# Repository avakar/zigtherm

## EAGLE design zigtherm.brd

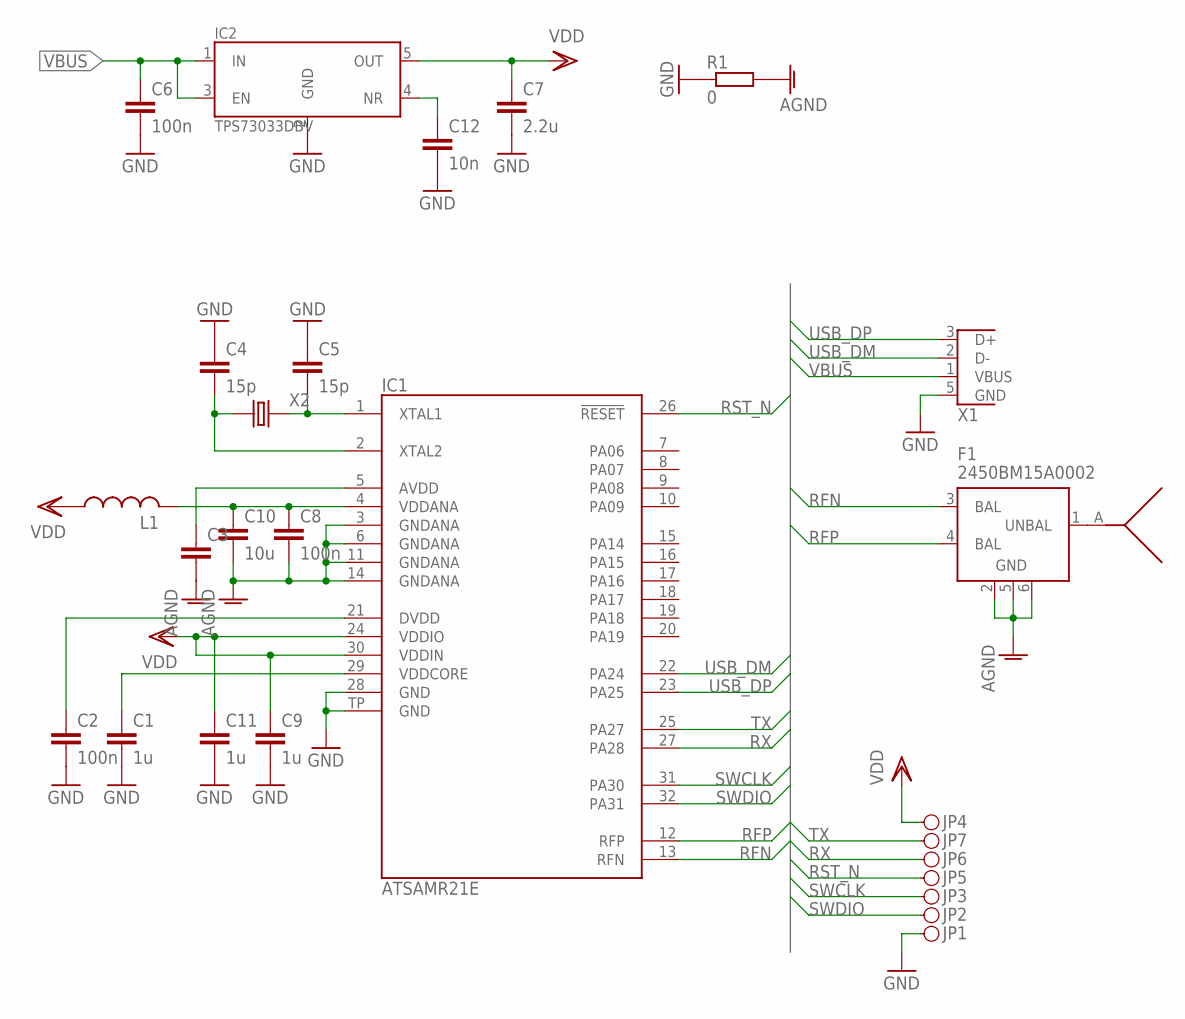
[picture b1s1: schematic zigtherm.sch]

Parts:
AE1: INVERTED_F_ANTENNA
C1, C9, C11: 1u; C0603
C2, C6, C8: 100n; C0603
C3: C-EUC0603; C0603
C4, C5: 15p; C0603
C7: 2.2u; C0603
C10: 10u; C0603
C12: 10n; C0603
F1: 2450BM15A0002
IC1: ATSAMR21E; QFN32
IC2: TPS73033DBV; SOT23-DBV
JP1, JP2, JP3, JP4, JP5, JP6, JP7: PINH1X01SMD
L1: L-USL2012C; L2012C
R1: 0; R0603
X1: USB-MICRO-B-BOTTOM-MOLEX
X2: XTAL3.2X2.5; 3.2X2.5

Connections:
AGND: C3.2, C8.2, C10.2, F1.2 (GND), F1.5 (GND), F1.6 (GND), IC1.3 (GNDANA), IC1.6 (GNDANA), IC1.11 (GNDANA), IC1.14 (GNDANA), R1.2
AVDD: C3.1, IC1.5 (AVDD)
DVDD: C2.1, IC1.21 (DVDD)
GND: C1.2, C2.2, C4.1, C5.1, C6.2, C7.2, C9.2, C11.2, C12.2, IC1.28 (GND), IC1.TP (GND), IC2.2 (GND), JP1.1, R1.1, X1.5 (GND)
unnamed: AE1.A, F1.1 (UNBAL)
unnamed: C12.1, IC2.4 (NR)
unnamed: C4.2, IC1.2 (XTAL2), X2.1
unnamed: C5.2, IC1.1 (XTAL1), X2.3 (2)
RFN: F1.3 (BAL), IC1.13 (RFN)
RFP: F1.4 (BAL), IC1.12 (RFP)
RST_N: IC1.26 (!RESET), JP5.1
RX: IC1.27 (PA28), JP6.1
SWCLK: IC1.31 (PA30), JP3.1
SWDIO: IC1.32 (PA31), JP2.1
TX: IC1.25 (PA27), JP7.1
USB_DM: IC1.22 (PA24), X1.2 (D-)
USB_DP: IC1.23 (PA25), X1.3 (D+)
VBUS: C6.1, IC2.1 (IN), IC2.3 (EN), X1.1 (VBUS)
VDD: C7.1, C9.1, C11.1, IC1.24 (VDDIO), IC1.30 (VDDIN), IC2.5 (OUT), JP4.1, L1.1
VDDANA: C8.1, C10.1, IC1.4 (VDDANA), L1.2
VDDCORE: C1.1, IC1.29 (VDDCORE)

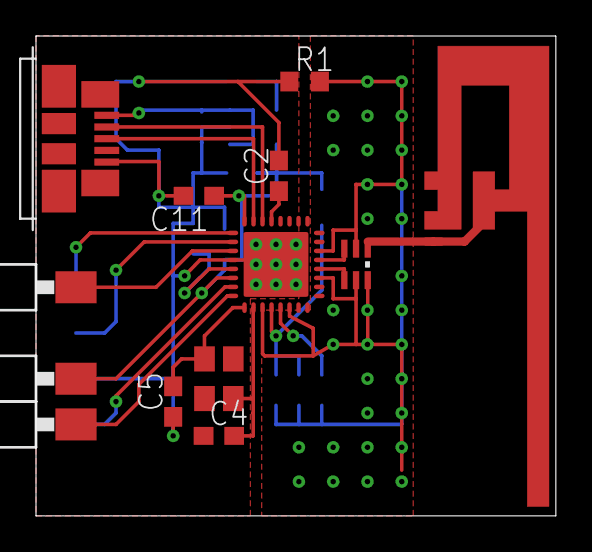
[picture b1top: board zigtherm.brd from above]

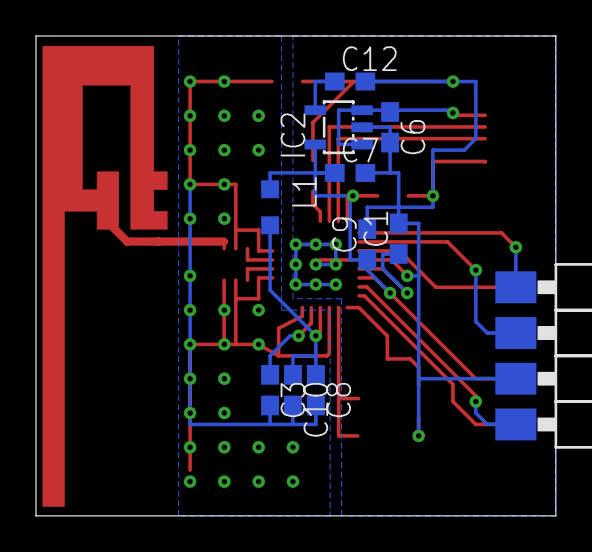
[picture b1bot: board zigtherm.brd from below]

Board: 2 copper layers, 28.9 x 26.7 mm, 27 parts (14 on the bottom side), 21 nets.

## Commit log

2015-12-06 Initial.
2015-12-07 Final design.
